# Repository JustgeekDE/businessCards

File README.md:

# Overview
This repository contains source files for my PCB business cards

There are currently 2 different types of cards:

## Power Supply
![Picture of power supply
card](powerSupply/powerSupply.jpeg)

This is a small breakout board for a 7805 linear voltage regulator made solely from through-hole
components.  
This board is mainly useful for people interested in learning more about electronics.

## Reference Card
![Picture of reference
card](referenceBoard/referenceCard.jpeg)

This board contains a series of examples of silkscreen sizes, component footprints and various design considerations.  
The aim is to provide a useful size reference when design PCBs on a computer.

# Producing copies of the boards
The board files are available as [Cadsoft EAGLE](https://cadsoft.io/) files.

When creating your own copy, make sure to check all layers and replace the appropriate texts with your information.  
There are placeholders in the silkscreen, stopmask and copper layers that need to be replaced.

The boards are sized smaller than any common business card format, to allow them to fit into the common 5cm x 5cm bucket
of affordable PCB production services. My personal favourite is [Dirty PCBs](http://dirtypcbs.com/) but any production
service should be able to produce the boards.

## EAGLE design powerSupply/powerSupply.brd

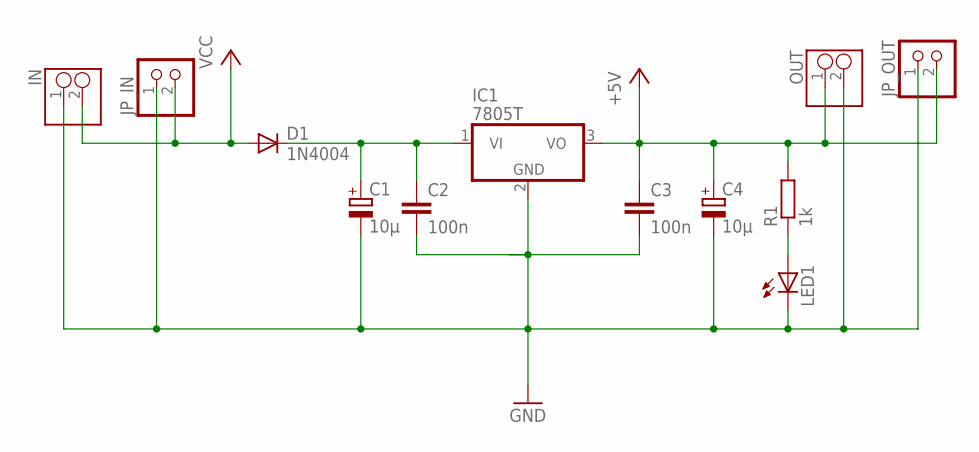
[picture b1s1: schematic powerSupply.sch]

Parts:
C1, C4: 10µ; E2,5-6
C2, C3: 100n; C025-024X044
D1: 1N4004; DO41-10
IC1: 7805T; TO220H
IN: GENERIC-1X2_PINWAGO-5MM; WAGO-5MM-2_PIN
JP_IN: PINHD-1X2; 1X02
JP_OUT: PINHD-1X2; 1X02
LED1: LED3MM
OUT: GENERIC-1X2_PINWAGO-5MM; WAGO-5MM-2_PIN
R1: 1k; 0207/7

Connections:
+5V: C3.1, C4.+, IC1.3 (VO), JP_OUT.2, OUT.1, R1.2
GND: C1.-, C2.2, C3.2, C4.-, IC1.2 (GND), IN.1, JP_IN.1, JP_OUT.1, LED1.K (C), OUT.2
unnamed: C1.+, C2.1, D1.C, IC1.1 (VI)
unnamed: LED1.A, R1.1
VCC: D1.A, IN.2, JP_IN.2

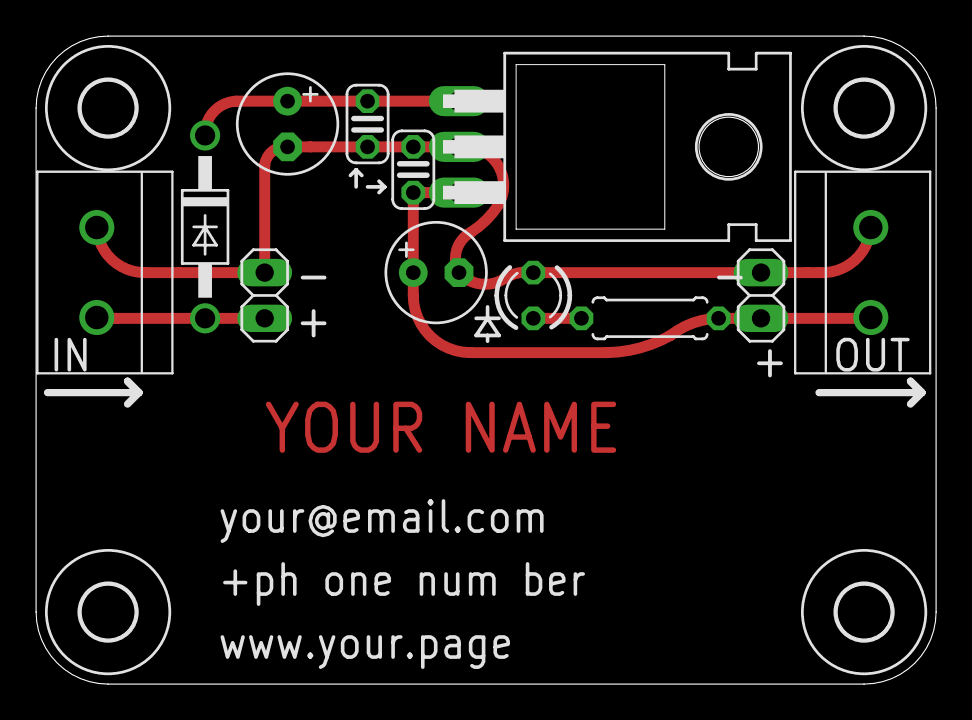
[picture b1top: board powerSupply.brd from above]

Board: 2 copper layers, 50.0 x 36.0 mm, 16 parts (0 on the bottom side), 5 nets.

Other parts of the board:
U$1, U$2, U$3, U$5: 3,0

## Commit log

2016-07-17 Adds example photos of the boards
2016-07-17 adds additional linebreak after images
2016-07-17 changes LICENSE to CC 4.0 BY which is more suitable to the content
